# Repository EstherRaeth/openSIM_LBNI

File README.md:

## open-source structured illumination add-on for fluorescence microscopes

The resolution of conventional optical microscopes is limited by light diffraction to about 200nm. Several superresolution techniques have been recently developed to overcome this limit. Among them, **SIM (structured illumination microscopy)** is one of the most suited for biological imaging.

The **open source hardware project openSIM** is an **add-on** designed at the *Laboratory for Bio- and Nano- Instrumentation (LBNI, EPFL)* (https://www.epfl.ch/labs/lbni/) to **upgrade conventional fluorescence microscopes for superresolution imaging**. The openSIM is an open-source hardware project which has been designed specifically so that it can be built easily by other researchers using the documentation. Our goal is to reach labs worldwide and build a vibrant **open-hardware community**.

**Here you can find a schematic of the general structure of the openSIM documentation**

A detailed documentation with all the information to build and use the openSIM is provided on our openSIM webpage: 
**https://opensim.notion.site/**

All the files that need to be downloaded in order to assemble and operate the openSIM can be found in this repository. 
More information about the structure of this repository can be found in the README file in the download folder.

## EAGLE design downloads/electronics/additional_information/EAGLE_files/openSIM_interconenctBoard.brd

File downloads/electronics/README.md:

**Electronics folder structure**

**Electronics folder content**

The files in the folder 'CAMOutputs' are required when ordering the PCB. 

(GerberFiles: Gerber files are a standard file format used in the manufacturing of printed circuit boards (PCBs). These files contain the information necessary to guide the PCB fabrication process and ensure that the PCB is manufactured to the design specifications. Gerber files typically include data on the various layers of the PCB, such as the copper traces, solder mask, silkscreen, drill holes, and other relevant features. PCB design software generates these files, and they are then provided to a PCB manufacturer for the production of the actual circuit board.)

In the folder 'additional information' information on the PCB population can be found. The folder contains also a subfolder 'EAGLE_files' containing the PCB design files (.brd, .sch) in case a user seeks more information or wants to modify the board. These files have to be opened with the Eagle (electronic design software). A free version of Eagle can be downloaded here: http://eagle.autodesk.com/eagle/software-versions/7

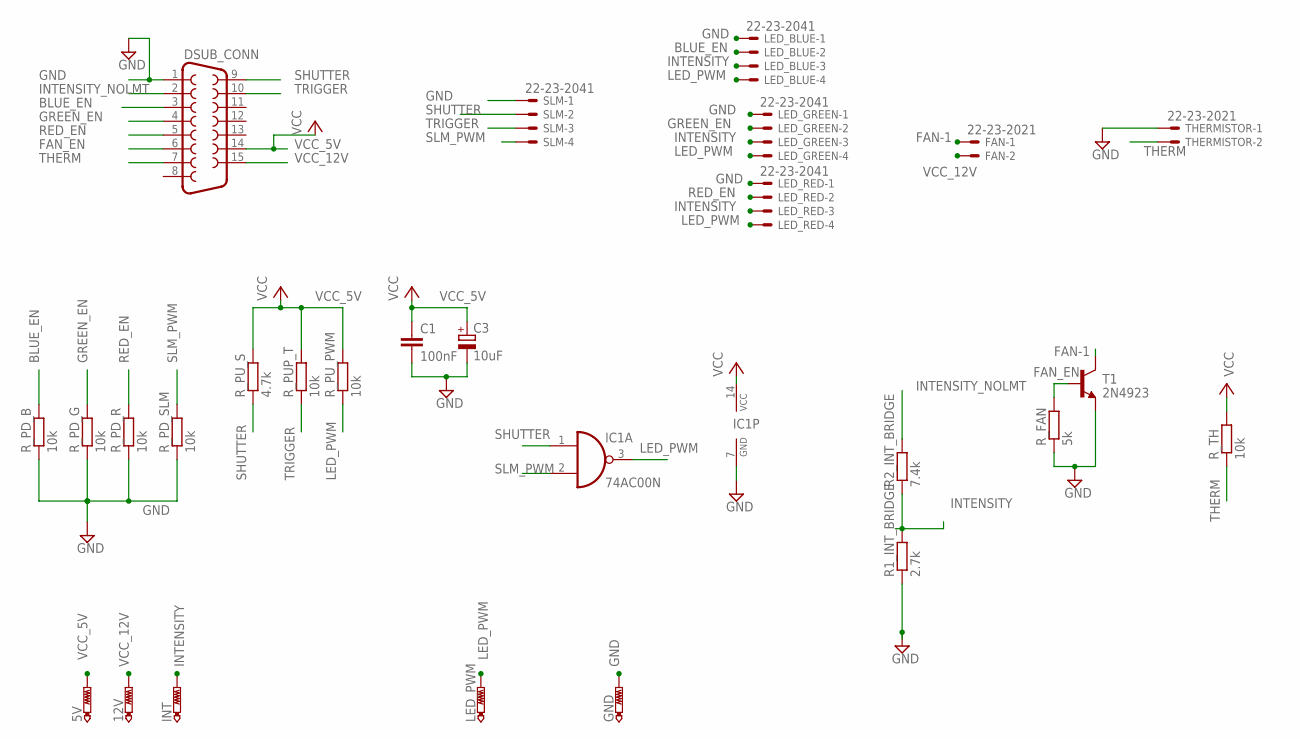
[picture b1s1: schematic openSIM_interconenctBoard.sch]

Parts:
5V, 12V: PTR1PAD1-20; P1-20
C1: 100nF; C050-025X075
C3: 10uF; E2,5-6E
DSUB_CONN: F15V
FAN: 22-23-2021
GND: PTR1PAD1-13Y; P1-13Y
IC1: 74AC00N; DIL14
INT: PTR1PAD1-20; P1-20
LED_BLUE: 22-23-2041
LED_GREEN: 22-23-2041
LED_PWM: PTR1PAD1-20; P1-20
LED_RED: 22-23-2041
R1_INT_BRIDGE: 2.7k; 0207/10
R2_INT_BRIDGE: 7.4k; 0207/10
R_FAN: 5k; 0207/10
R_PD_B: 10k; 0207/10
R_PD_G: 10k; 0207/10
R_PD_R: 10k; 0207/10
R_PD_SLM: 10k; 0207/10
R_PUP_T: 10k; 0207/10
R_PU_PWM: 10k; 0207/10
R_PU_S: 4.7k; 0207/10
R_TH: 10k; 0207/10
SLM: 22-23-2041
T1: 2N4923; TO126
THERMISTOR: 22-23-2021

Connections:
BLUE_EN: DSUB_CONN.3, LED_BLUE.2, R_PD_B.2
FAN-1: FAN.1, T1.2 (C)
FAN_EN: DSUB_CONN.6, R_FAN.2, T1.3 (B)
GND: C1.2, C3.-, DSUB_CONN.1, GND.TP, IC1.7 (GND), LED_BLUE.1, LED_GREEN.1, LED_RED.1, R1_INT_BRIDGE.1, R_FAN.1, R_PD_B.1, R_PD_G.1, R_PD_R.1, R_PD_SLM.1, SLM.1, T1.1 (E), THERMISTOR.1
GREEN_EN: DSUB_CONN.4, LED_GREEN.2, R_PD_G.2
INTENSITY: INT.TP, LED_BLUE.3, LED_GREEN.3, LED_RED.3, R1_INT_BRIDGE.2, R2_INT_BRIDGE.1
INTENSITY_NOLMT: DSUB_CONN.2, R2_INT_BRIDGE.2
LED_PWM: IC1.3 (O), LED_BLUE.4, LED_GREEN.4, LED_PWM.TP, LED_RED.4, R_PU_PWM.1
RED_EN: DSUB_CONN.5, LED_RED.2, R_PD_R.2
SHUTTER: DSUB_CONN.9, IC1.1 (I0), R_PU_S.1, SLM.2
SLM_PWM: IC1.2 (I1), R_PD_SLM.2, SLM.4
THERM: DSUB_CONN.7, R_TH.1, THERMISTOR.2
TRIGGER: DSUB_CONN.10, R_PUP_T.1, SLM.3
VCC_5V: 5V.TP, C1.1, C3.+, DSUB_CONN.14, IC1.14 (VCC), R_PUP_T.2, R_PU_PWM.2, R_PU_S.2, R_TH.2
VCC_12V: 12V.TP, DSUB_CONN.15, FAN.2

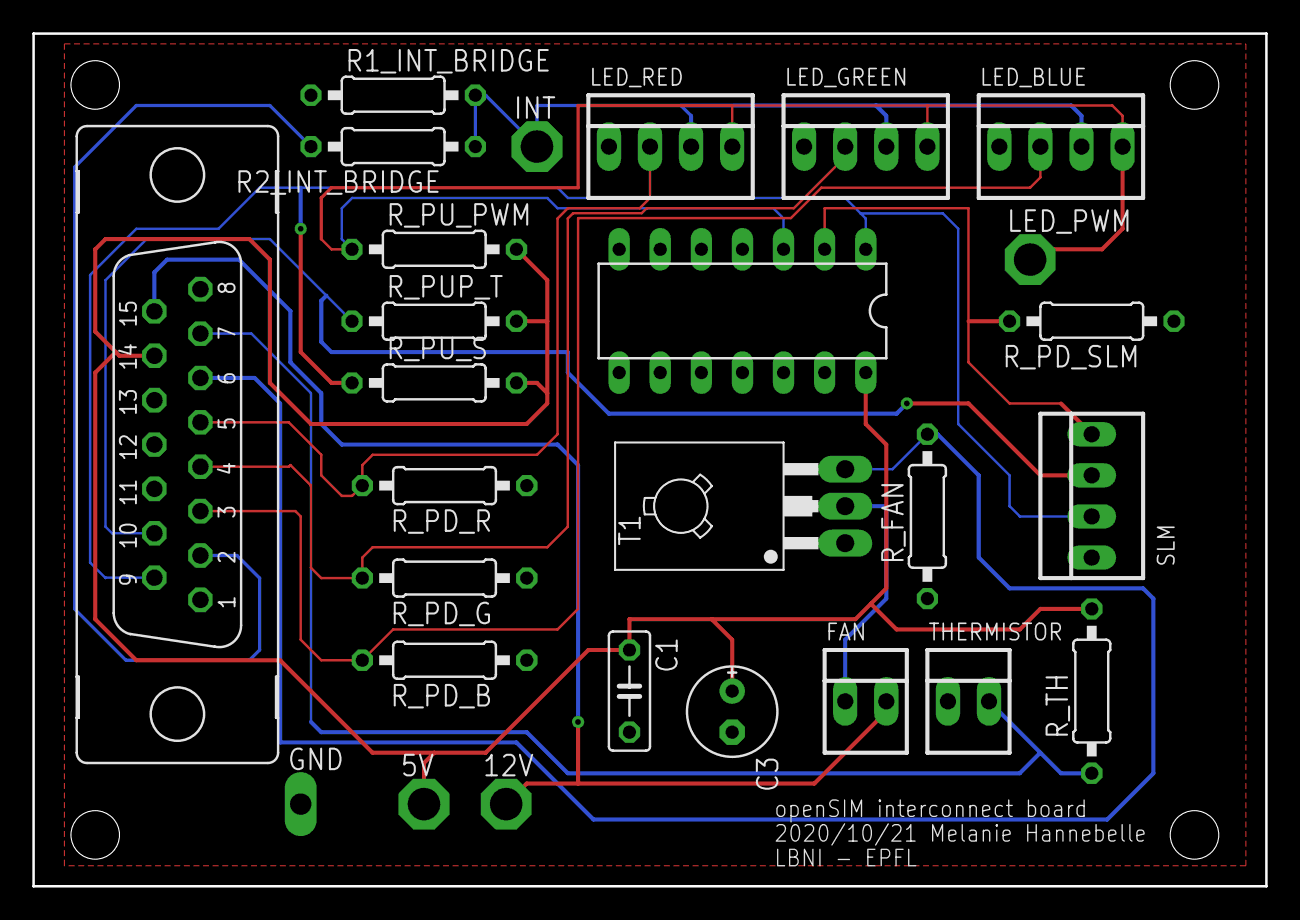
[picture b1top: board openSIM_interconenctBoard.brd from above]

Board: 2 copper layers, 76.2 x 52.7 mm, 27 parts (0 on the bottom side), 15 nets.

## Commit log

2023-01-13 Create downloads
2023-01-13 Create description
2023-01-13 Update description
2023-01-13 Create read_me
2023-01-13 Rename description to README
2023-11-01 Rename README.md to README.md
2023-11-02 upload files
2023-11-02 upload updated user manual
2023-11-02 upload software
2023-11-02 upload software 2
